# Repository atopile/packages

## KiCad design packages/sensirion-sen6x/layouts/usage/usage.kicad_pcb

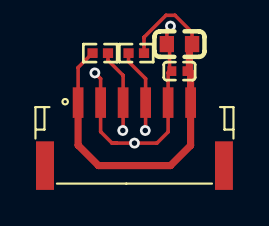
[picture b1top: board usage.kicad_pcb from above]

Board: 2 copper layers, 5 parts (0 on the bottom side), 4 nets.

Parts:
C1: 9.999F; C0603
C2: 1F; C0402
CN1: CONN-TH_SM06B-GHS-TB-LF-SN
R1, R2: 4700Ω; R0402

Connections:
SCL: CN1.4, R1.1
SDA: CN1.3, R2.1
hv: C1.1, C2.1, CN1.1, CN1.6, R1.2, R2.2
lv: C1.2, C2.2, CN1.2, CN1.5

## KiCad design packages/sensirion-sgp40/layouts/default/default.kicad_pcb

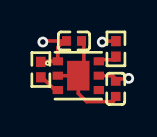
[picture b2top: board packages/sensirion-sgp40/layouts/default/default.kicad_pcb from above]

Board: 2 copper layers, 5 parts (0 on the bottom side), 5 nets.

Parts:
C1, C2: 1±10.0%F; C0402
R1, R2: 10000±1.0%Ω; R0402
U1: DFN-6_L2.4-W2.4-P0.80-TL-EP

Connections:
SCL: R1.2, U1.6
SDA: R2.2, U1.3
decoupling_cap_heater-power-hv: C2.1, U1.5
hv: C1.1, R1.1, R2.1, U1.1
lv: C1.2, C2.2, U1.2, U1.7

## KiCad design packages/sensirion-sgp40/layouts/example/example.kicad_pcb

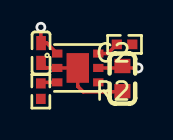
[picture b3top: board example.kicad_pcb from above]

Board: 2 copper layers, 5 parts (0 on the bottom side), 5 nets.

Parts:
C1: 1µF ±10% 50V X5R; C0603
C2: 100nF ±10% 16V X7R; C0402
R1, R2: 10kΩ ±1% 62.5mW; R0402
U1: DFN-6_L2.4-W2.4-P0.80-TL-EP

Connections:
SCL: R1.1, U1.6
SDA: R2.1, U1.3
VDD: C1.1, C2.1, U1.1, U1.5
gnd: C1.2, C2.2, U1.2, U1.7
hv: R1.2, R2.2

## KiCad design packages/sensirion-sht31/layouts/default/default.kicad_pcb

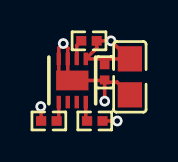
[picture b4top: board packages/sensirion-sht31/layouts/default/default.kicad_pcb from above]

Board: 2 copper layers, 6 parts (0 on the bottom side), 5 nets.

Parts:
C1: 1F; C0402
C2: 9.999F; C0805
R1, R2, R3: 10000Ω; R0402
S1: DFN-8_L2.5-W2.5-P0.50-BL-EP

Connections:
NRESET: R1.2, S1.6
SCL: R2.1, S1.4
SDA: R3.1, S1.1
hv: C1.1, C2.1, R1.1, R2.2, R3.2, S1.5
lv: C1.2, C2.2, S1.2, S1.7, S1.8, S1.9

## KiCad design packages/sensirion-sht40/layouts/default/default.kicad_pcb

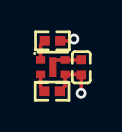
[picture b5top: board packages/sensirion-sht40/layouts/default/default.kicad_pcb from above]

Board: 2 copper layers, 4 parts (0 on the bottom side), 4 nets.

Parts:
C1: 1F; C0402
R1, R2: 10000Ω; R0402
U1: DFN-4_L1.5-W1.5-P0.8-TL-EP

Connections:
SCL: R1.1, U1.2
SDA: R2.1, U1.1
hv: C1.1, R1.2, R2.2, U1.3
lv: C1.2, U1.4, U1.5
